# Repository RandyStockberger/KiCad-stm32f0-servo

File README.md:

# KiCad-stm32f0-servo
KiCad files for a stm32f030 based railroad turnout controller driven by RC servos

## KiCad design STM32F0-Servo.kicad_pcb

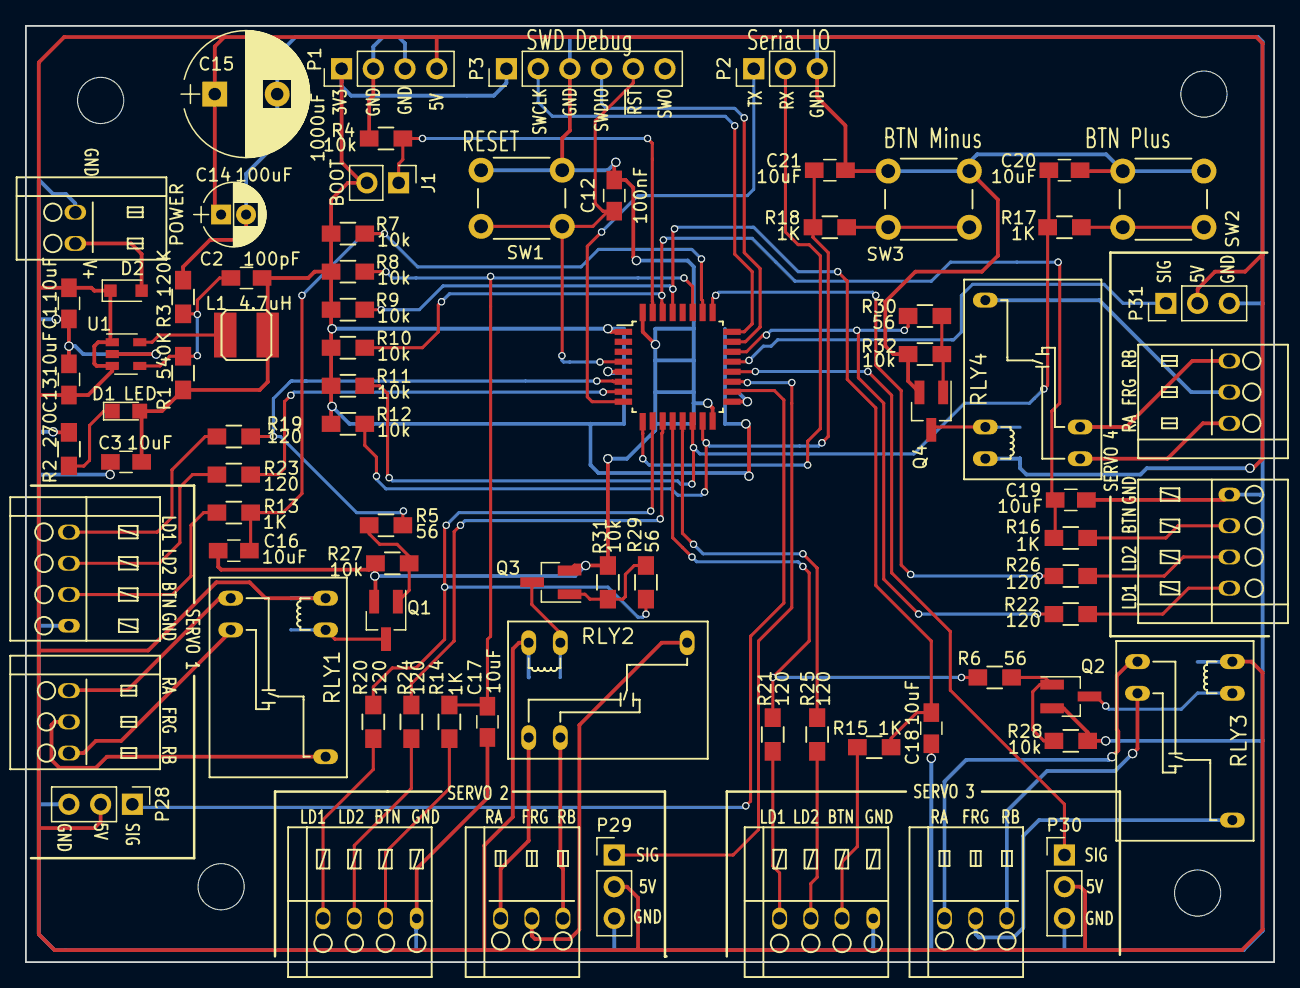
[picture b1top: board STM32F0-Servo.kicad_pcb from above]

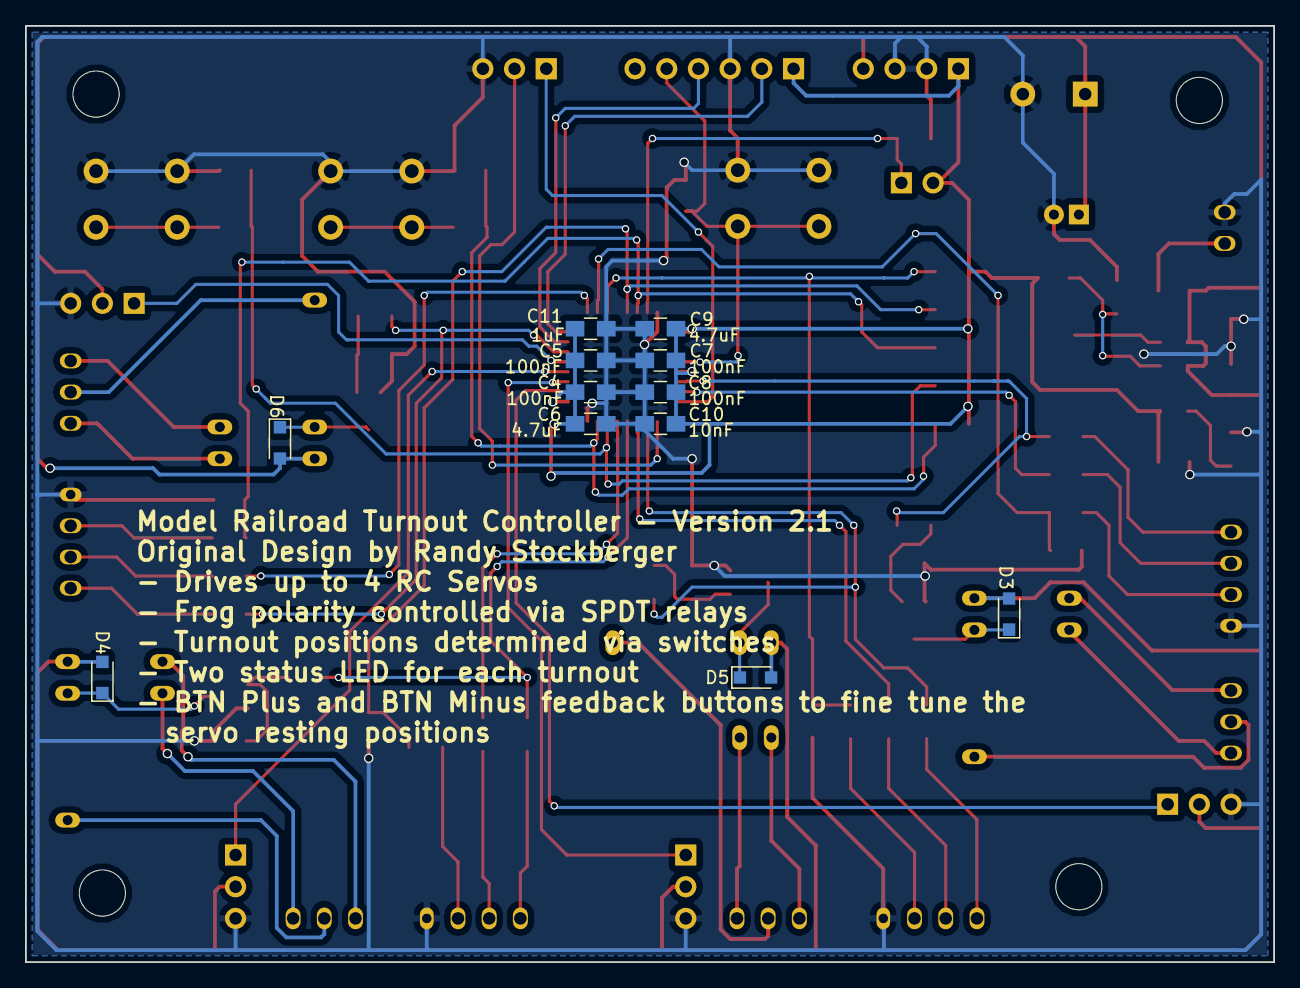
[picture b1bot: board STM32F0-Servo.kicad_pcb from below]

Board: 2 copper layers, 100.0 x 75.0 mm, 90 parts (12 on the bottom side), 65 nets.

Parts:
C1, C3, C13, C16, C17, C18, C19, C20, C21: 10uF; C_0805_HandSoldering
C2: 100pF; C_0805_HandSoldering
C4, C5, C7, C8, C12: 100nF; C_0805_HandSoldering
C6, C9: 4.7uF; C_0805_HandSoldering
C10: 10nF; C_0805_HandSoldering
C11: 1uF; C_0805_HandSoldering
C14: 100uF; CP_Radial_D5.0mm_P2.00mm
C15: 1000uF; CP_Radial_D10.0mm_P5.00mm
D1: LED; LED_0805
D2, D3, D4, D5, D6: DIODE; D_SOD-323_HandSoldering
J1: BOOT; Pin_Header_Straight_1x02_Pitch2.54mm
J2: POWER; Phoenix-Combicon-2.5mm-2
J5: SV1_LDBTN; Phoenix-Combicon-2.5mm-4
J6: SV2_LDBTN; Phoenix-Combicon-2.5mm-4
J7: SV3_LDBTN; Phoenix-Combicon-2.5mm-4
J8: SV4_LDBTN; Phoenix-Combicon-2.5mm-4
L1: 4.7uH; Bourns-Inductor-SRN4026
P1: DBG POWER; Pin_Header_Straight_1x04_Pitch2.54mm
P2: SERIAL; Pin_Header_Straight_1x03_Pitch2.54mm
P3: SWD-DEBUG; Pin_Header_Straight_1x06_Pitch2.54mm
P4: FROG1; Phoenix-Combicon-2.5mm-3
P5: FROG3; Phoenix-Combicon-2.5mm-3
P6: FROG4; Phoenix-Combicon-2.5mm-3
P7: FROG2; Phoenix-Combicon-2.5mm-3
P28: SERVO1; Pin_Header_Straight_1x03_Pitch2.54mm
P29: SERVO2; Pin_Header_Straight_1x03_Pitch2.54mm
P30: SERVO3; Pin_Header_Straight_1x03_Pitch2.54mm
P31: SERVO4; Pin_Header_Straight_1x03_Pitch2.54mm
Q1, Q2, Q3, Q4: MMBF170; SOT-23_Handsoldering
R1: 540K; R_0805_HandSoldering
R2: 270; R_0805_HandSoldering
R3: 120K; R_0805_HandSoldering
R4, R7, R8, R9, R10, R11, R12, R27, R28, R31, R32: 10k; R_0805_HandSoldering
R5, R6, R29, R30: 56; R_0805_HandSoldering
R13, R14, R15, R16, R17, R18: 1K; R_0805_HandSoldering
R19, R20, R21, R22, R23, R24, R25, R26: 120; R_0805_HandSoldering
RLY1, RLY2, RLY3, RLY4: Relay-SPDT-TE_Connectivity-Form_C; RELAY_SPDT
SW1: Reset; SW_PUSH_6mm_h4.3mm
SW2: BTPLUS; SW_PUSH_6mm_h4.3mm
SW3: BTMINUS; SW_PUSH_6mm_h4.3mm
U1: PAM2305DABADJ; SOT-23-5
U2: STM32F03-LQFP32; LQFP-32_7x7mm_Pitch0.8mm

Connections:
+3V3: C2.1, C3.1, C4.1, C5.1, C6.1, C7.1, C8.1, C9.1, C10.1, C11.1, D1.2, J1.2, L1.2, P1.1, P3.1, R1.1, R7.1, R8.1, R9.1, R10.1, R11.1, R12.1, U2.1, U2.5, U2.17
+5V: C1.1, C13.1, C14.1, C15.1, D2.1, D3.2, D4.2, D5.2, D6.2, P1.4, P28.2, P29.2, P30.2, P31.2, RLY1.12, RLY2.12, RLY3.12, RLY4.12, U1.1, U1.3
/BOOT0: J1.1, R4.1, U2.31
/BT1: C16.2, R7.2, R13.1, U2.26
/BT2: C17.2, R8.2, R14.1, U2.27
/BT3: C18.2, R9.2, R15.1, U2.29
/BT4: C19.2, R10.2, R16.1, U2.30
/BTMINUS: C21.2, R12.2, R18.1, U2.15
/BTN1: J5.3, R13.2
/BTN2: J6.3, R14.2
/BTN3: J7.3, R15.2
/BTN4: J8.3, R16.2
/BTPLUS: C20.2, R11.2, R17.1, U2.14
/FROG1: P4.2, RLY1.7
/FROG2: P7.2, RLY2.7
/FROG3: P5.2, RLY3.7
/FROG4: P6.2, RLY4.7
/LD1A: R5.2, R19.2, U2.6
/LD1B: R23.2, U2.7
/LD2A: R20.2, R29.2, U2.10
/LD2B: R24.2, U2.11
/LD3A: R6.2, R21.2, U2.12
/LD3B: R25.2, U2.13
/LD4A: R22.2, R30.2, U2.22
/LD4B: R26.2, U2.25
/NRST: C12.1, P3.5, SW1.2, U2.4
/RAIL1A: P4.3, RLY1.2
/RAIL1B: P4.1, RLY1.1
/RAIL2A: P7.3, RLY2.2
/RAIL2B: P7.1, RLY2.1
/RAIL3A: P5.3, RLY3.2
/RAIL3B: P5.1, RLY3.1
/RAIL4A: P6.3, RLY4.2
/RAIL4B: P6.1, RLY4.1
/RX: P2.2, U2.9
/SV1: P28.1, U2.18
/SV2: P29.1, U2.19
/SV3: P30.1, U2.20
/SV4: P31.1, U2.21
/SWCLK: P3.2, U2.24
/SWDIO: P3.4, U2.23
/TX: P2.1, U2.8
/VIN: D2.2, J2.2
GND: C1.2, C3.2, C4.2, C5.2, C6.2, C7.2, C8.2, C9.2, C10.2, C11.2, C12.2, C13.2, C14.2, C15.2, C16.1, C17.1, C18.1, C19.1, C20.1, C21.1, J2.1, J5.4, J6.4, J7.4, J8.4, P1.2, P1.3, P2.3, P3.3, P28.3, P29.3, P30.3, P31.3, Q1.2, Q2.2, Q3.2, Q4.2, R2.1, R3.2, R4.2, R27.2, R28.2, R31.2, R32.2, SW1.1, SW2.2, SW3.2, U1.2, U2.16, U2.32
unnamed: C2.2, R1.2, R3.1, U1.4
unnamed: D1.1, R2.2
unnamed: D3.1, Q1.3, RLY1.11
unnamed: D4.1, Q2.3, RLY3.11
unnamed: D5.1, Q3.3, RLY2.11
unnamed: D6.1, Q4.3, RLY4.11
unnamed: J5.1, R19.1
unnamed: J5.2, R23.1
unnamed: J6.1, R20.1
unnamed: J6.2, R24.1
unnamed: J7.1, R21.1
unnamed: J7.2, R25.1
unnamed: J8.1, R22.1
unnamed: J8.2, R26.1
unnamed: L1.1, U1.5
unnamed: Q1.1, R5.1, R27.1
unnamed: Q2.1, R6.1, R28.1
unnamed: Q3.1, R29.1, R31.1
unnamed: Q4.1, R30.1, R32.1
unnamed: R17.2, SW2.1
unnamed: R18.2, SW3.1

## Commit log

2017-01-29 Initial checkin of existing files to new project
2017-01-29 Added Gerbers directory to ignore list
2017-02-06 Final edits for Ver 2.1, PCBs ordered from this version
